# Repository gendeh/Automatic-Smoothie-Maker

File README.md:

# Automatic-Smoothie-Maker
ECE 445 - Team 49's KiCad project for Automatic Smoothie Maker.

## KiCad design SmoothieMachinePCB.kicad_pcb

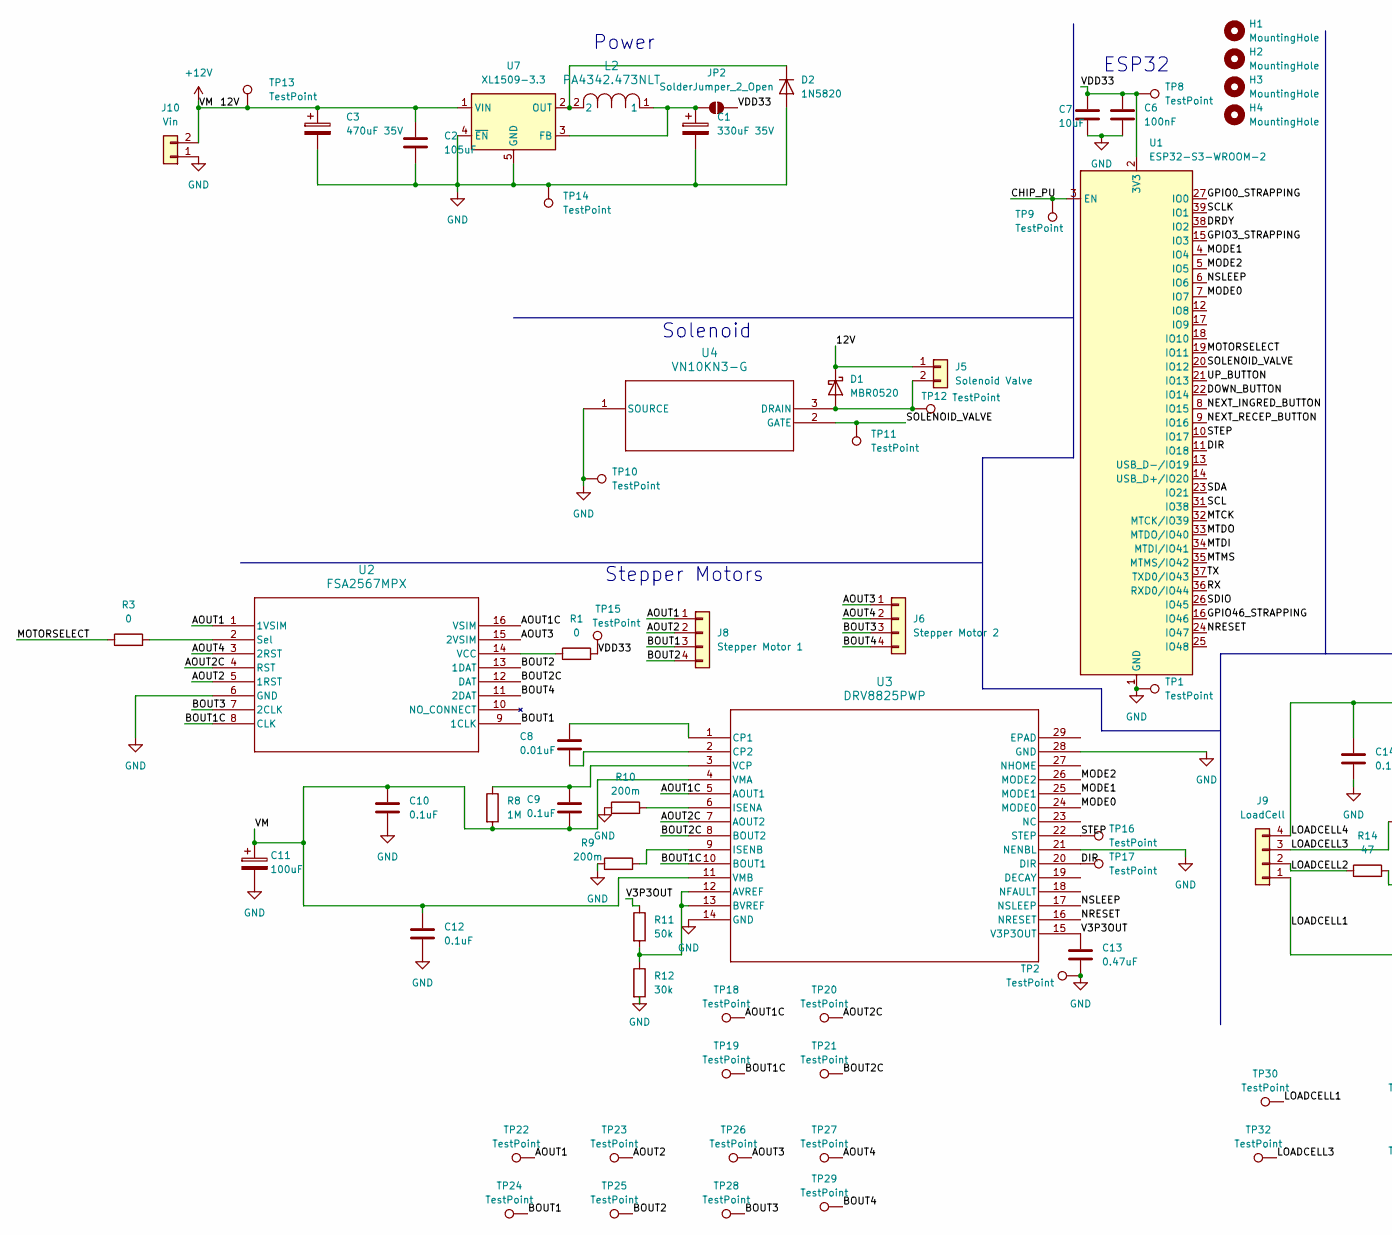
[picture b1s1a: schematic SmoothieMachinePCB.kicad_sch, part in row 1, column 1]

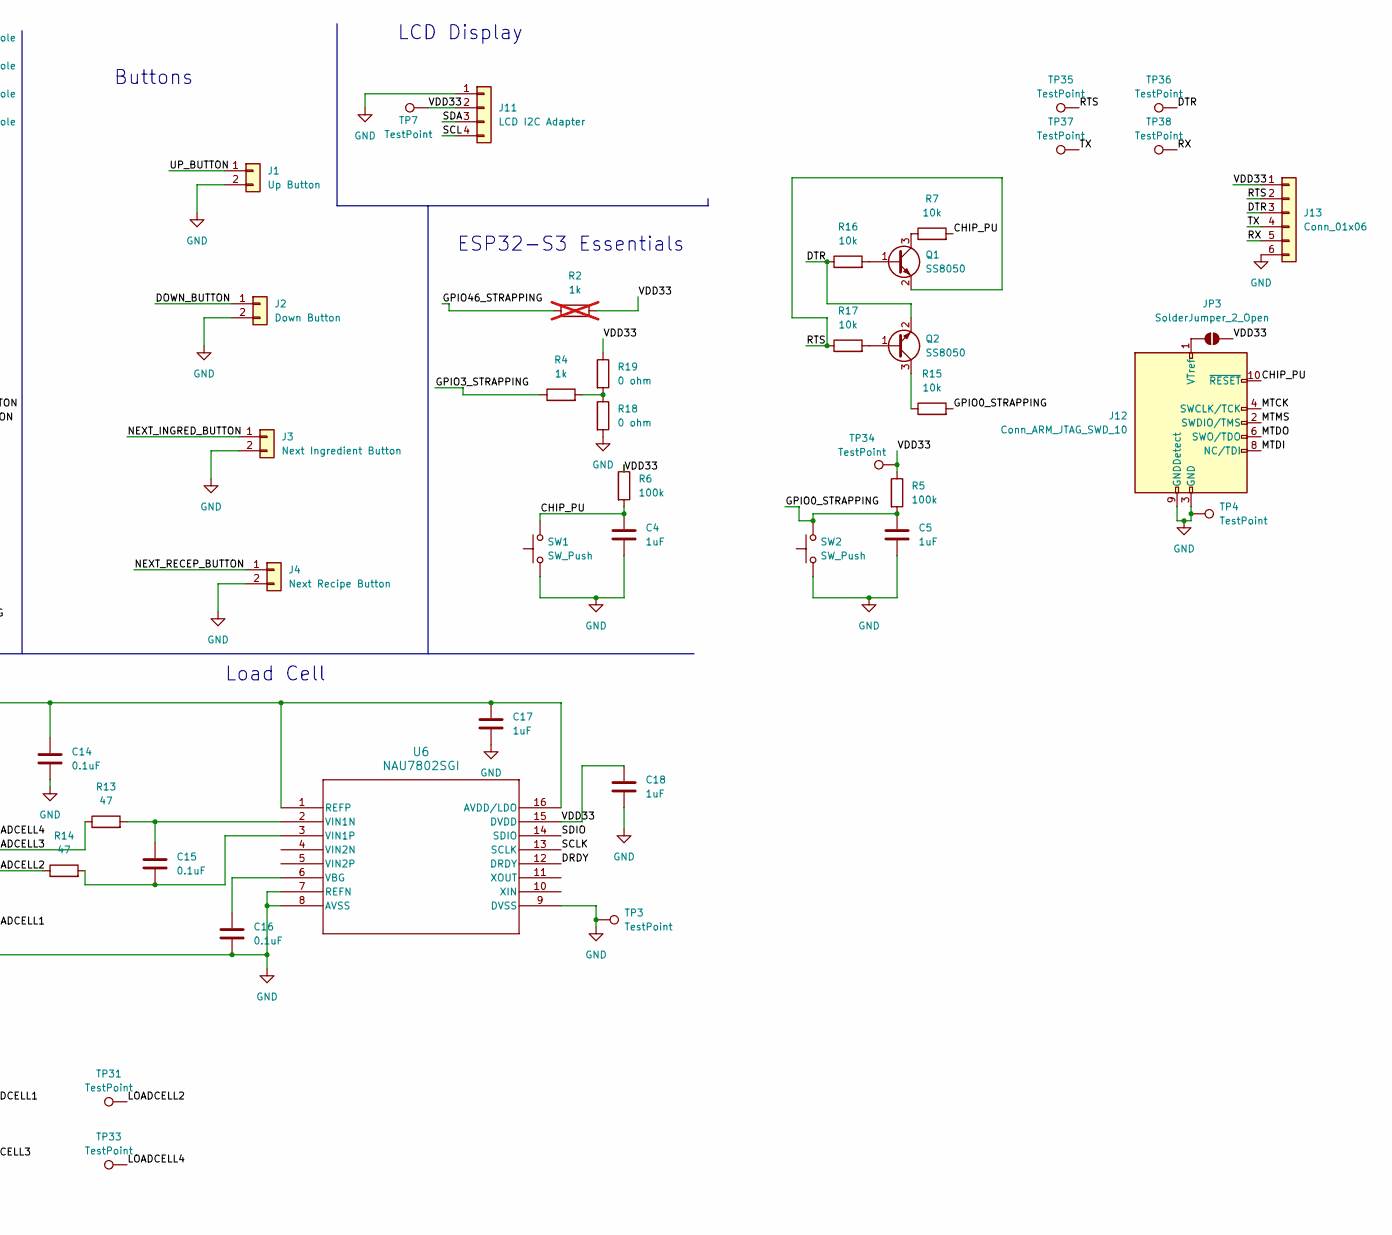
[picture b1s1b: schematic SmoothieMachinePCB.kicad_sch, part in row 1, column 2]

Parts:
C1: 330uF 35V; CP_Elec_10x12.5
C2: 105uF; CAP_EMK325AB_3P2X2P5_TAY
C3: 470uF 35V; CAP_UUG_12P5X21_NCH
C4, C5, C17, C18: 1uF; C_0805_2012Metric_Pad1.18x1.45mm_HandSolder
C6: 100nF; C_0805_2012Metric_Pad1.18x1.45mm_HandSolder
C7: 10uF; C_0805_2012Metric_Pad1.18x1.45mm_HandSolder
C8: 0.01uF; C_0805_2012Metric_Pad1.18x1.45mm_HandSolder
C9, C10, C12, C14, C15, C16: 0.1uF; C_0805_2012Metric_Pad1.18x1.45mm_HandSolder
C11: 100uF; U2-I_NCH
C13: 0.47uF; C_0805_2012Metric_Pad1.18x1.45mm_HandSolder
D1: MBR0520; D_SOD-123
D2: 1N5820; CR_0-E3&slash_54_VIS
H1, H2, H3, H4: MountingHole; MountingHole_3.2mm_M3
J1: Up Button; Molex_KK-254_AE-6410-02A_1x02_P2.54mm_Vertical
J2: Down Button; Molex_KK-254_AE-6410-02A_1x02_P2.54mm_Vertical
J3: Next Ingredient Button; Molex_KK-254_AE-6410-02A_1x02_P2.54mm_Vertical
J4: Next Recipe Button; Molex_KK-254_AE-6410-02A_1x02_P2.54mm_Vertical
J5: Solenoid Valve; Molex_KK-254_AE-6410-02A_1x02_P2.54mm_Vertical
J6: Stepper Motor 2; Molex_KK-254_AE-6410-04A_1x04_P2.54mm_Vertical
J8: Stepper Motor 1; Molex_KK-254_AE-6410-04A_1x04_P2.54mm_Vertical
J9: LoadCell; Molex_KK-254_AE-6410-04A_1x04_P2.54mm_Vertical
J10: Vin; Molex_KK-254_AE-6410-02A_1x02_P2.54mm_Vertical
J11: LCD I2C Adapter; Molex_KK-254_AE-6410-04A_1x04_P2.54mm_Vertical
J12: Conn_ARM_JTAG_SWD_10; IDC-Header_2x05_P2.54mm_Vertical
J13: Conn_01x06; Molex_KK-254_AE-6410-06A_1x06_P2.54mm_Vertical
JP2, JP3: SolderJumper_2_Open; SolderJumper-2_P1.3mm_Open_TrianglePad1.0x1.5mm
L2: PA4342.473NLT; IND_PA4342_FOOTPRINT2_PUL
Q1, Q2: SS8050; SOT-23
R1, R3: 0; R_0805_2012Metric_Pad1.20x1.40mm_HandSolder
R2: 1k; R_0805_2012Metric_Pad1.20x1.40mm_HandSolder; not fitted
R4: 1k; R_0805_2012Metric_Pad1.20x1.40mm_HandSolder
R5, R6: 100k; R_0805_2012Metric_Pad1.20x1.40mm_HandSolder
R7, R15, R16, R17: 10k; R_0805_2012Metric_Pad1.20x1.40mm_HandSolder
R8: 1M; R_0805_2012Metric_Pad1.20x1.40mm_HandSolder
R9, R10: 200m; R_0805_2012Metric_Pad1.20x1.40mm_HandSolder
R11: 50k; R_0805_2012Metric_Pad1.20x1.40mm_HandSolder
R12: 30k; R_0805_2012Metric_Pad1.20x1.40mm_HandSolder
R13, R14: 47; R_0805_2012Metric_Pad1.20x1.40mm_HandSolder
R18, R19: 0 ohm; R_0805_2012Metric_Pad1.20x1.40mm_HandSolder
SW1, SW2: SW_Push; SW_SPST_B3S-1000
TP1, TP2, TP3, TP4, TP7, TP8, TP9, TP10, TP11, TP12, TP13, TP14, TP15, TP16, TP17, TP18, TP19, TP20, TP21, TP22, TP23, TP24, TP25, TP26, TP27, TP28, TP29, TP30, TP31, TP32, TP33, TP34, TP35, TP36, TP37, TP38: TestPoint; TestPoint_Keystone_5010-5014_Multipurpose
U1: ESP32-S3-WROOM-2
U2: FSA2567MPX; UMLP16_1P8X2P6_ONS
U3: DRV8825PWP; PWP28_5P18X3P1
U4: VN10KN3-G; TO-92_MC_MCH
U6: NAU7802SGI; SOI16_NAU7802SGI_NUV
U7: XL1509-3.3; SOIC-8_3.9x4.9mm_P1.27mm

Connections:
+12V: C2.1, C3.1, C9.2, C10.1, C11.1, C12.1, D1.1 (K), J5.1, J10.2, R8.2, TP13.1, U3.4 (VMA), U3.11 (VMB), U7.1 (VIN)
/AOUT1: J8.1, TP22.1, U2.1 (1VSIM)
/AOUT1C: TP18.1, U2.16 (VSIM), U3.5 (AOUT1)
/AOUT2: J8.2, TP23.1, U2.5 (1RST)
/AOUT2C: TP20.1, U2.4 (RST), U3.7 (AOUT2)
/AOUT3: J6.1, TP26.1, U2.15 (2VSIM)
/AOUT4: J6.2, TP27.1, U2.3 (2RST)
/BOUT1: J8.3, TP24.1, U2.9 (1CLK)
/BOUT1C: TP19.1, U2.8 (CLK), U3.10 (BOUT1)
/BOUT2: J8.4, TP25.1, U2.13 (1DAT)
/BOUT2C: TP21.1, U2.12 (DAT), U3.8 (BOUT2)
/BOUT3: J6.3, TP28.1, U2.7 (2CLK)
/BOUT4: J6.4, TP29.1, U2.11 (2DAT)
/CHIP_PU: C4.1, J12.10 (~RESET), R6.2, R7.2, SW1.2, TP9.1, U1.3 (EN)
/DIR: TP17.1, U1.11 (IO18), U3.20 (DIR)
/DOWN_BUTTON: J2.1, U1.22 (IO14)
/DRDY: U1.38 (IO2), U6.12 (DRDY)
/DTR: J13.3, Q2.2 (E), R16.1, TP36.1
/GPIO0_STRAPPING: C5.1, R5.2, R15.2, SW2.2, U1.27 (IO0)
/GPIO3_STRAPPING: R4.1, U1.15 (IO3)
/GPIO46_STRAPPING: R2.1, U1.16 (IO46)
/LOADCELL2: J9.2, R14.1, TP31.1
/LOADCELL3: J9.3, R13.1, TP32.1
/LOADCELL4: C14.1, C17.1, J9.4, TP33.1, U6.1 (REFP), U6.16 (AVDD/LDO)
/MODE0: U1.7 (IO7), U3.24 (MODE0)
/MODE1: U1.4 (IO4), U3.25 (MODE1)
/MODE2: U1.5 (IO5), U3.26 (MODE2)
/MOTORSELECT: R3.1, U1.19 (IO11)
/MTCK: J12.4 (SWCLK/TCK), U1.32 (MTCK/IO39)
/MTDI: J12.8 (NC/TDI), U1.34 (MTDI/IO41)
/MTDO: J12.6 (SWO/TDO), U1.33 (MTDO/IO40)
/MTMS: J12.2 (SWDIO/TMS), U1.35 (MTMS/IO42)
/NEXT_INGRED_BUTTON: J3.1, U1.8 (IO15)
/NEXT_RECEP_BUTTON: J4.1, U1.9 (IO16)
/NRESET: U1.24 (IO47), U3.16 (NRESET)
/NSLEEP: U1.6 (IO6), U3.17 (NSLEEP)
/RTS: J13.2, Q1.2 (E), R17.1, TP35.1
/RX: J13.5, TP38.1, U1.36 (RXD0/IO44)
/SCL: J11.4, U1.31 (IO38)
/SCLK: U1.39 (IO1), U6.13 (SCLK)
/SDA: J11.3, U1.23 (IO21)
/SDIO: U1.26 (IO45), U6.14 (SDIO)
/SOLENOID_VALVE: TP11.1, U1.20 (IO12), U4.2 (GATE)
/STEP: TP16.1, U1.10 (IO17), U3.22 (STEP)
/TX: J13.4, TP37.1, U1.37 (TXD0/IO43)
/UP_BUTTON: J1.1, U1.21 (IO13)
/V3P3OUT: C13.1, R11.1, U3.15 (V3P3OUT)
/VDD33: C6.1, C7.1, C18.1, J11.2, J13.1, JP2.2 (B), JP3.2 (B), R1.2, R2.2, R5.1, R6.1, R19.1, TP7.1, TP8.1, TP15.1, TP34.1, U1.2 (3V3), U6.15 (DVDD)
GND: C1.2, C2.2, C3.2, C4.2, C5.2, C6.2, C7.2, C10.2, C11.2, C12.2, C13.2, C14.2, C16.2, C17.2, C18.2, D2.2 (A), J1.2, J2.2, J3.2, J4.2, J9.1, J10.1, J11.1, J12.3 (GND), J12.5 (GND), J12.9 (GNDDetect), J13.6, R9.1, R10.1, R12.2, R18.2, SW1.1, SW2.1, TP1.1, TP2.1, TP3.1, TP4.1, TP10.1, TP14.1, TP30.1, U1.1 (GND), U1.40 (GND), U1.41 (GND), U2.6 (GND), U3.14 (GND), U3.21 (NENBL), U3.28 (GND), U4.1 (SOURCE), U6.7 (REFN), U6.8 (AVSS), U6.9 (DVSS), U7.4 (~EN), U7.5 (GND), U7.6 (GND), U7.7 (GND), U7.8 (GND)
unnamed: D1.2 (A), J5.2, TP12.1, U4.3 (DRAIN)
unnamed: D2.1 (K), L2.2, U7.2 (OUT)
unnamed: J12.1 (VTref), JP3.1 (A)
unnamed: C1.1, JP2.1 (A), L2.1, U7.3 (FB)
unnamed: Q1.1 (B), R16.2
unnamed: Q1.3 (C), R7.1
unnamed: Q2.1 (B), R17.2
unnamed: Q2.3 (C), R15.1
unnamed: R4.2, R18.1, R19.2
unnamed: R3.2, U2.2 (Sel)
unnamed: R1.1, U2.14 (VCC)
unnamed: R11.2, R12.1, U3.12 (AVREF), U3.13 (BVREF)
unnamed: C8.1, U3.1 (CP1)
unnamed: C8.2, U3.2 (CP2)
unnamed: R10.2, U3.6 (ISENA)
unnamed: R9.2, U3.9 (ISENB)
unnamed: C9.1, R8.1, U3.3 (VCP)
unnamed: C16.1, U6.6 (VBG)
unnamed: C15.1, R13.2, U6.2 (VIN1N)
unnamed: C15.2, R14.2, U6.3 (VIN1P)

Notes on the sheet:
Load Cell
Power
Stepper Motors
ESP32
Buttons
LCD Display
ESP32-S3 Essentials
Solenoid

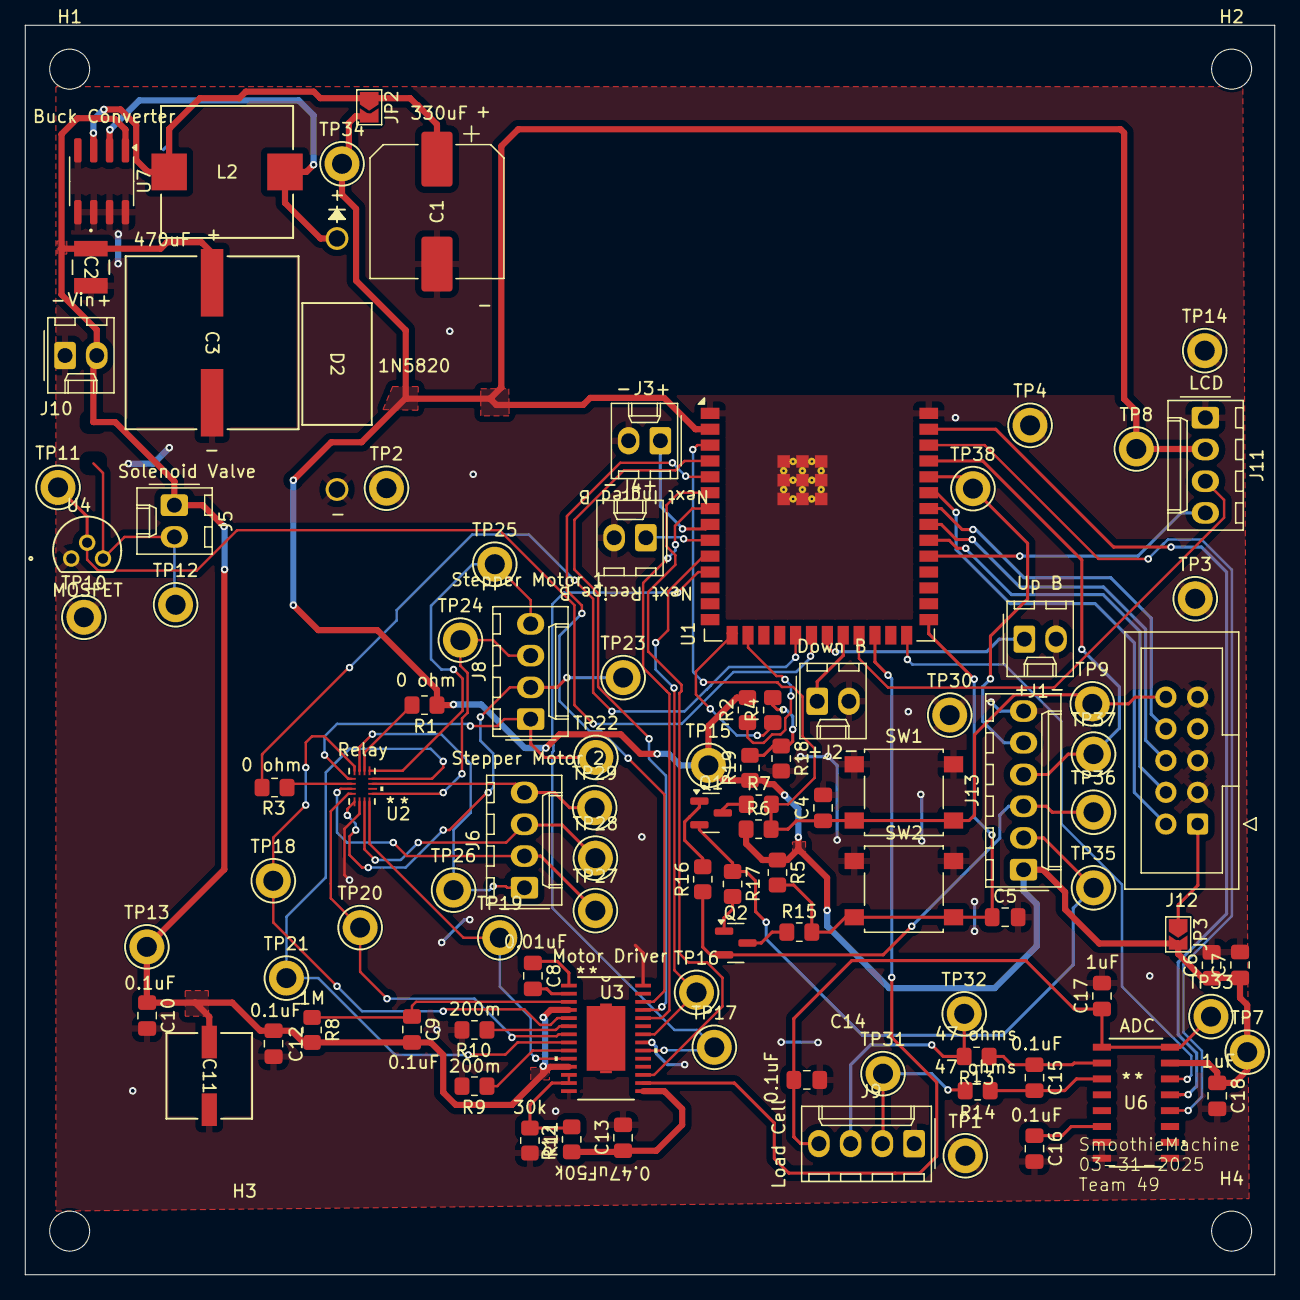
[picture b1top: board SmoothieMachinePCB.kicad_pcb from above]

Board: 2 copper layers, 100.0 x 100.0 mm, 104 parts (1 on the bottom side), 69 nets.

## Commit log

2025-03-01 Initial commit of KiCad project
2025-03-02 Committing main four files
2025-03-02 Testing
2025-03-02 Deleting unnecessary files
2025-03-02 Added motor driver
2025-03-02 Added LED
2025-03-03 First basically complete schematic of PCB
2025-03-07 Changed LCD Display to 1x4 connector, removed debouncing circuits, and added mounting holes
2025-03-13 Finished footprint assignments, have to place and route
2025-03-13 Added downloaded footprint folders
2025-03-13 Adding .DS_Store file
2025-03-25 Second round pcb files
2025-03-30 Labeled basically everything
2025-04-05 Integrated Microcontroller Essential Stuff into Schematic and Assigned Footprints
2025-04-05 Changed resistor from 0.1 to 0.01 uF in DRV8825PWP top left
2025-04-15 Fourth wave ordered pcb files
2025-04-22 Fixed incorrect capacitor value
